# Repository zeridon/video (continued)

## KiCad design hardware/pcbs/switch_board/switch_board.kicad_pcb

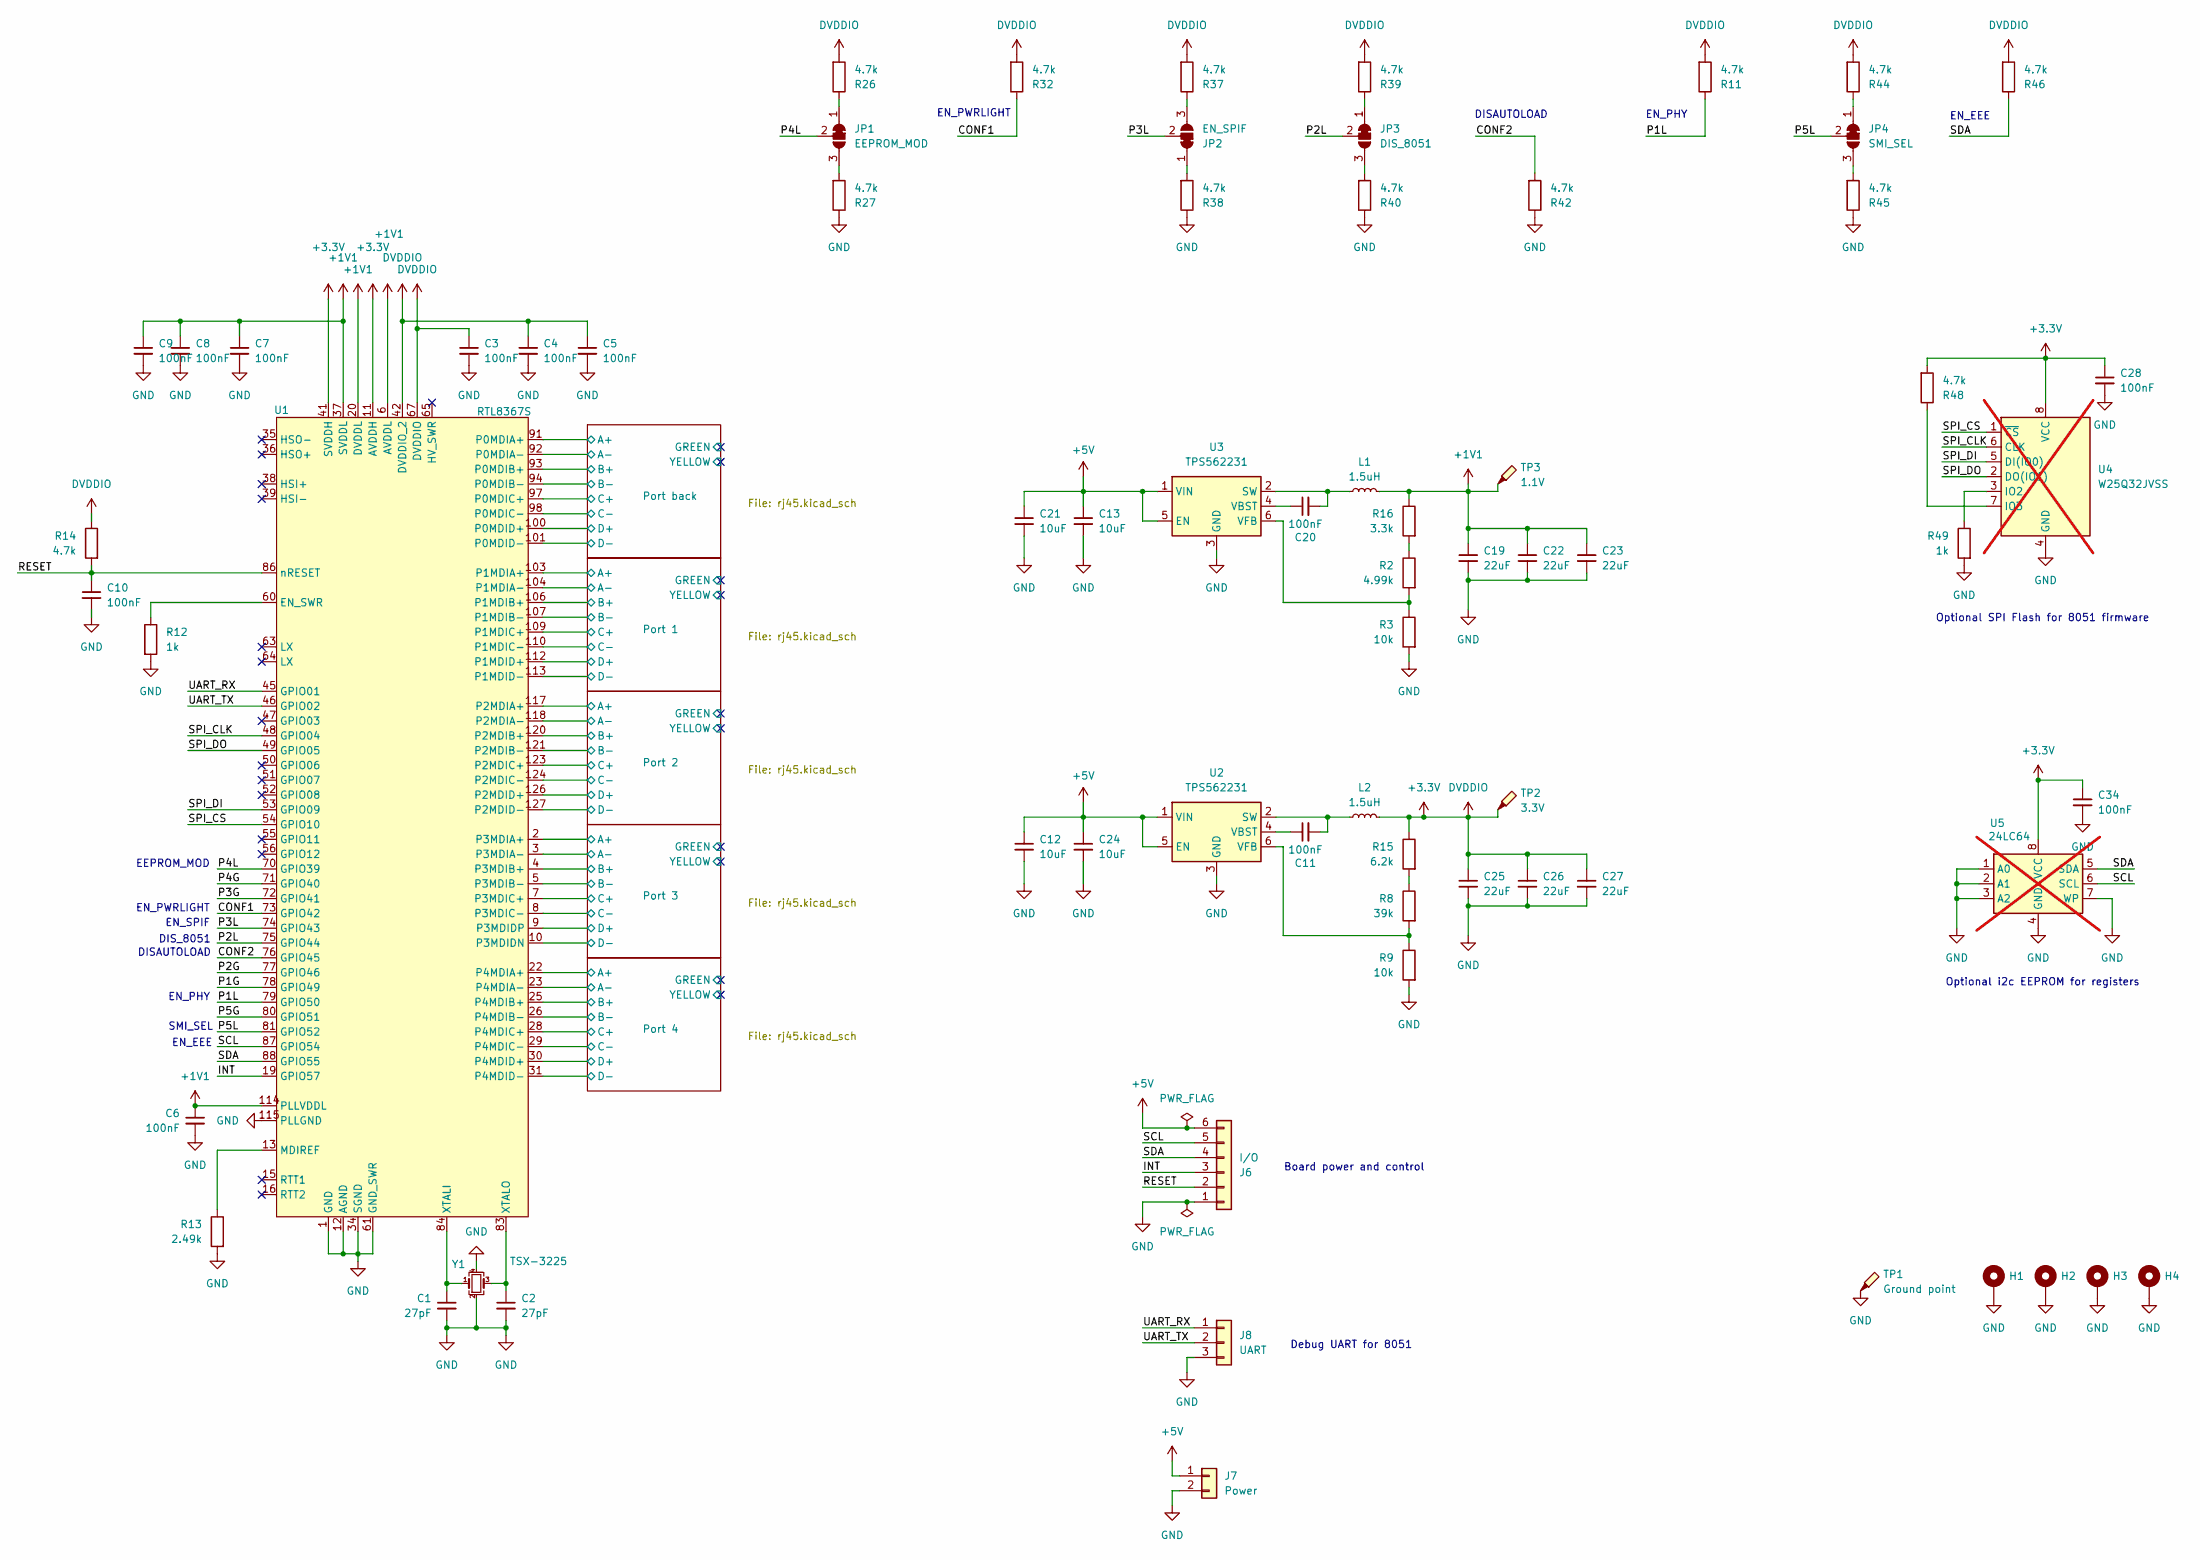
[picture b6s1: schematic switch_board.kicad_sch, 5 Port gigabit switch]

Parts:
C1, C2: 27pF; C_0603_1608Metric; Part C 27pF 16V 0603; LCSC C107045
C3, C4, C5, C6, C7, C8, C9, C10, C28, C34: 100nF; C_0603_1608Metric; Part C 100nF 16V 0603; LCSC C14663
C11, C20: 100nF; C_0603_1608Metric_Pad1.08x0.95mm_HandSolder; MPN 885012206126; LCSC C14663
C12, C13, C21, C24: 10uF; C_0603_1608Metric_Pad1.08x0.95mm_HandSolder; MPN 885012206126; LCSC C96446
C19, C22, C23, C25, C26, C27: 22uF; C_0603_1608Metric_Pad1.08x0.95mm_HandSolder; MPN 885012206126; LCSC C59461
H1, H2, H3, H4: MountingHole_Pad; MountingHole_3.2mm_M3_Pad_Via
J6: I/O; mta100_01x6_P2.54_647050-6; Part 640456-6; LCSC C86506
J7: Power; mta100_01x2_P2.54_647050-2; Part 640456-2; LCSC C86502
J8: UART; PinHeader_1x03_P1.00mm_Vertical
JP1: EEPROM_MOD; SolderJumper-3_P1.3mm_Bridged12_RoundedPad1.0x1.5mm
JP2: EN_SPIF; SolderJumper-3_P1.3mm_Bridged12_RoundedPad1.0x1.5mm
JP3: DIS_8051; SolderJumper-3_P1.3mm_Bridged12_RoundedPad1.0x1.5mm
JP4: SMI_SEL; SolderJumper-3_P1.3mm_Bridged12_RoundedPad1.0x1.5mm
L1, L2: 1.5uH; L_Taiyo-Yuden_MD-5050; Part BWVF005050201R5T00 or 74404054015; LCSC C702825
R2: 4.99k; R_0603_1608Metric; Part R 4.99kΩ 125mW 1% 0603; LCSC C23046
R3, R9: 10k; R_0603_1608Metric; Part R 10kΩ 125mW 1% 0603; LCSC C25804
R8: 39k; R_0603_1608Metric; Part R 39kΩ 125mW 1% 0603; LCSC C23153
R11, R14, R26, R27, R32, R37, R38, R39, R40, R42, R44, R45, R46, R48: 4.7k; R_0603_1608Metric; Part R 4.7kΩ 125mW 1% 0603; LCSC C23162
R12, R49: 1k; R_0603_1608Metric; Part R 1kΩ 125mW 1% 0603; LCSC C21190
R13: 2.49k; R_0402_1005Metric; Part R 2.49kΩ 125mW 1% 0402; LCSC C145071
R15: 6.2k; R_0603_1608Metric; Part R 6.2kΩ 125mW 1% 0603; LCSC C4160
R16: 3.3k; R_0603_1608Metric; Part R 3.3kΩ 125mW 1% 0603; LCSC C22978
TP1: Ground point; TestPoint_Bridge_Pitch2.54mm_Drill1.0mm
TP2: 3.3V; TestPoint_THTPad_2.0x2.0mm_Drill1.0mm
TP3: 1.1V; TestPoint_THTPad_2.0x2.0mm_Drill1.0mm
U1: RTL8367S; LQFP-128_14x14mm_P0.4mm; Part RTL8367S; LCSC C2760849
U2, U3: TPS562231; SOT-563; Part TPS562231DRLR; LCSC C2070899
U4: W25Q32JVSS; SOIC-8_5.23x5.23mm_P1.27mm; not fitted
U5: 24LC64; SOIC-8_3.9x4.9mm_P1.27mm; not fitted
Y1: TSX-3225; Crystal_SMD_SeikoEpson_TSX3225-4Pin_3.2x2.5mm; Part X322525MOB4SI; LCSC C9006

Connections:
+1V1: C6.1, C7.1, C8.1, C9.1, C19.1, C22.1, C23.1, L1.2, R16.1, TP3.1, U1.6 (AVDDL), U1.14 (AVDDL), U1.20 (DVDDL), U1.27 (AVDDL), U1.37 (SVDDL), U1.58 (DVDDL), U1.69 (DVDDL), U1.95 (AVDDL), U1.108 (AVDDL), U1.114 (PLLVDDL), U1.122 (AVDDL)
+3.3V: C3.1, C4.1, C5.1, C25.1, C26.1, C27.1, C28.1, C34.1, L2.2, R11.2, R14.1, R15.1, R26.2, R32.2, R37.2, R39.2, R44.2, R46.2, R48.2, TP2.1, U1.11 (AVDDH), U1.17 (AVDDH), U1.21 (AVDDH), U1.33 (AVDDH), U1.41 (SVDDH), U1.42 (DVDDIO_2), U1.59 (DVDDIO_2), U1.67 (DVDDIO), U1.82 (AVDDH), U1.90 (AVDDH), U1.102 (AVDDH), U1.116 (AVDDH), U1.128 (AVDDH), U4.8 (VCC), U5.8 (VCC)
+5V: C12.1, C13.1, C21.1, C24.1, J6.6, J7.1, U2.1 (VIN), U2.5 (EN), U3.1 (VIN), U3.5 (EN)
/CONF1: R32.1, U1.73 (GPIO42)
/CONF2: R42.2, U1.76 (GPIO45)
/INT: J6.3, U1.19 (GPIO57)
/P1G: U1.78 (GPIO49)
/P1L: R11.1, U1.79 (GPIO50)
/P2G: U1.77 (GPIO46)
/P2L: JP3.2 (C), U1.75 (GPIO44)
/P3G: U1.72 (GPIO41)
/P3L: JP2.2 (C), U1.74 (GPIO43)
/P4G: U1.71 (GPIO40)
/P4L: JP1.2 (C), U1.70 (GPIO39)
/P5G: U1.80 (GPIO51)
/P5L: JP4.2 (C), U1.81 (GPIO52)
/Port 1/A+: U1.103 (P1MDIA+); also elsewhere on the board
/Port 1/A-: U1.104 (P1MDIA-); also elsewhere on the board
/Port 1/B+: U1.106 (P1MDIB+); also elsewhere on the board
/Port 1/B-: U1.107 (P1MDIB-); also elsewhere on the board
/Port 1/C+: U1.109 (P1MDIC+); also elsewhere on the board
/Port 1/C-: U1.110 (P1MDIC-); also elsewhere on the board
/Port 1/D+: U1.112 (P1MDID+); also elsewhere on the board
/Port 1/D-: U1.113 (P1MDID-); also elsewhere on the board
/Port 2/A+: U1.117 (P2MDIA+); also elsewhere on the board
/Port 2/A-: U1.118 (P2MDIA-); also elsewhere on the board
/Port 2/B+: U1.120 (P2MDIB+); also elsewhere on the board
/Port 2/B-: U1.121 (P2MDIB-); also elsewhere on the board
/Port 2/C+: U1.123 (P2MDIC+); also elsewhere on the board
/Port 2/C-: U1.124 (P2MDIC-); also elsewhere on the board
/Port 2/D+: U1.126 (P2MDID+); also elsewhere on the board
/Port 2/D-: U1.127 (P2MDID-); also elsewhere on the board
/Port 3/A+: U1.2 (P3MDIA+); also elsewhere on the board
/Port 3/A-: U1.3 (P3MDIA-); also elsewhere on the board
/Port 3/B+: U1.4 (P3MDIB+); also elsewhere on the board
/Port 3/B-: U1.5 (P3MDIB-); also elsewhere on the board
/Port 3/C+: U1.7 (P3MDIC+); also elsewhere on the board
/Port 3/C-: U1.8 (P3MDIC-); also elsewhere on the board
/Port 3/D+: U1.9 (P3MDIDP); also elsewhere on the board
/Port 3/D-: U1.10 (P3MDIDN); also elsewhere on the board
/Port 4/A+: U1.22 (P4MDIA+); also elsewhere on the board
/Port 4/A-: U1.23 (P4MDIA-); also elsewhere on the board
/Port 4/B+: U1.25 (P4MDIB+); also elsewhere on the board
/Port 4/B-: U1.26 (P4MDIB-); also elsewhere on the board
/Port 4/C+: U1.28 (P4MDIC+); also elsewhere on the board
/Port 4/C-: U1.29 (P4MDIC-); also elsewhere on the board
/Port 4/D+: U1.30 (P4MDID+); also elsewhere on the board
/Port 4/D-: U1.31 (P4MDID-); also elsewhere on the board
/Port back/A+: U1.91 (P0MDIA+); also elsewhere on the board
/Port back/A-: U1.92 (P0MDIA-); also elsewhere on the board
/Port back/B+: U1.93 (P0MDIB+); also elsewhere on the board
/Port back/B-: U1.94 (P0MDIB-); also elsewhere on the board
/Port back/C+: U1.97 (P0MDIC+); also elsewhere on the board
/Port back/C-: U1.98 (P0MDIC-); also elsewhere on the board
/Port back/D+: U1.100 (P0MDID+); also elsewhere on the board
/Port back/D-: U1.101 (P0MDID-); also elsewhere on the board
/RESET: C10.1, J6.2, R14.2, U1.86 (nRESET)
/SCL: J6.5, U1.87 (GPIO54), U5.6 (SCL)
/SDA: J6.4, R46.1, U1.88 (GPIO55), U5.5 (SDA)
/SPI_CLK: U1.48 (GPIO04), U4.6 (CLK)
/SPI_CS: U1.54 (GPIO10), U4.1 (~CS)
/SPI_DI: U1.53 (GPIO09), U4.5 (DI(IO0))
/SPI_DO: U1.49 (GPIO05), U4.2 (DO(IO1))
/UART_RX: J8.1, U1.45 (GPIO01)
/UART_TX: J8.2, U1.46 (GPIO02)
GND: C1.2, C2.2, C3.2, C4.2, C5.2, C6.2, C7.2, C8.2, C9.2, C10.2, C12.2, C13.2, C19.2, C21.2, C22.2, C23.2, C24.2, C25.2, C26.2, C27.2, C28.2, C34.2, H1.1, H2.1, H3.1, H4.1, J6.1, J7.2, J8.3, R3.2, R9.2, R12.2, R13.2, R27.1, R38.1, R40.1, R42.1, R45.1, R49.2, TP1.1, U1.1 (GND), U1.12 (AGND), U1.18 (GND), U1.24 (GND), U1.32 (GND), U1.34 (SGND), U1.40 (SGND), U1.43 (GND), U1.44 (GND), U1.57 (GND), U1.61 (GND_SWR), U1.62 (GND_SWR), U1.68 (GND), U1.85 (GND), U1.89 (GND), U1.96 (GND), U1.99 (GND), U1.105 (GND), U1.111 (GND), U1.115 (PLLGND), U1.119 (GND), U1.125 (GND), U2.3 (GND), U3.3 (GND), U4.4 (GND), U5.1 (A0), U5.2 (A1), U5.3 (A2), U5.4 (GND), U5.7 (WP), Y1.2, Y1.4; also elsewhere on the board
unnamed: JP1.1 (A), R26.1
unnamed: JP1.3 (B), R27.2
unnamed: JP2.1 (A), R38.2
unnamed: JP2.3 (B), R37.1
unnamed: JP3.1 (A), R39.1
unnamed: JP3.3 (B), R40.2
unnamed: JP4.1 (A), R44.1
unnamed: JP4.3 (B), R45.2
unnamed: R8.1, R15.2
unnamed: R2.1, R16.2
unnamed: R12.1, U1.60 (EN_SWR)
unnamed: R13.1, U1.13 (MDIREF)
unnamed: C1.1, U1.84 (XTALI), Y1.1
unnamed: C2.1, U1.83 (XTALO), Y1.3
unnamed: C11.2, L2.1, U2.2 (SW)
unnamed: C11.1, U2.4 (VBST)
unnamed: R8.2, R9.1, U2.6 (VFB)
unnamed: C20.2, L1.1, U3.2 (SW)
unnamed: C20.1, U3.4 (VBST)
unnamed: R2.2, R3.1, U3.6 (VFB)
unnamed: R49.1, U4.3 (IO2)
unnamed: R48.1, U4.7 (IO3)

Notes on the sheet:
EN_EEE
Board power and control
EN_PWRLIGHT
Optional i2c EEPROM for registers
DISAUTOLOAD
SMI_SEL
EN_PHY
EN_SPIF
Debug UART for 8051
Optional SPI Flash for 8051 firmware
EEPROM_MOD
DIS_8051

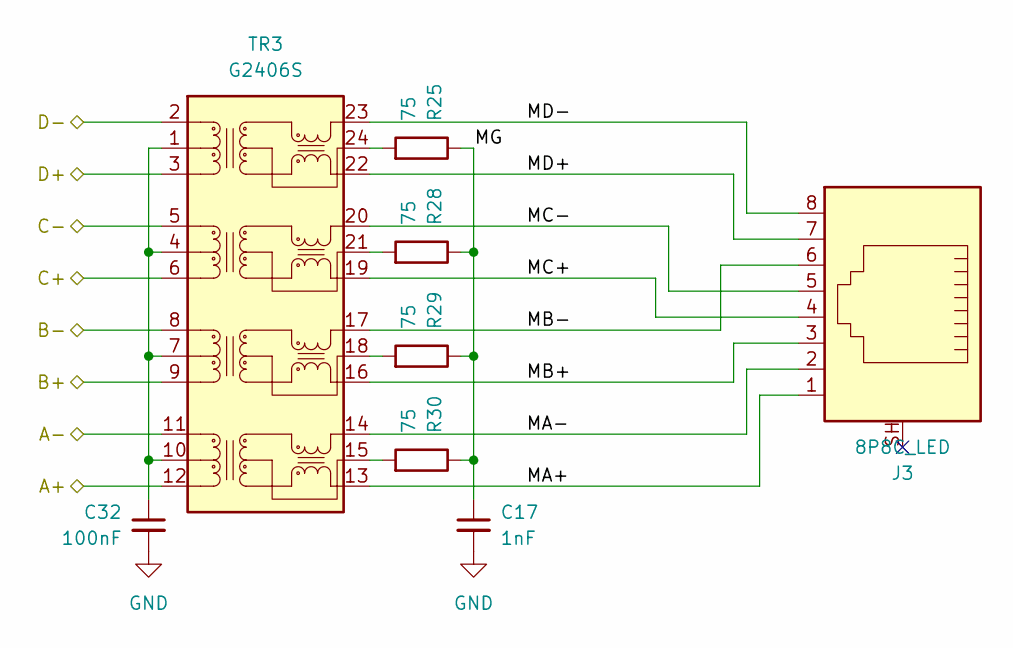
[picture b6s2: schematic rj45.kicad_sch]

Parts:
C17: 1nF; C_0603_1608Metric; Part C 1nF 16V 0603; LCSC C1588
C32: 100nF; C_0603_1608Metric; Part C 100nF 16V 0603; LCSC C14663
J3: 8P8C_LED; Heling MJ88-B211-JRS3; Part MJ88-B211-JRS3; LCSC C2895614
R25, R28, R29, R30: 75; R_0603_1608Metric; Part R 75Ω 125mW 1% 0603; LCSC C4275
TR3: G2406S; Part G2406S; LCSC C507595

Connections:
/Port 3/A+: TR3.12 (TD4-); also elsewhere on the board
/Port 3/A-: TR3.11 (TD4+); also elsewhere on the board
/Port 3/B+: TR3.9 (TD3-); also elsewhere on the board
/Port 3/B-: TR3.8 (TD3+); also elsewhere on the board
/Port 3/C+: TR3.6 (TD2-); also elsewhere on the board
/Port 3/C-: TR3.5 (TD2+); also elsewhere on the board
/Port 3/D+: TR3.3 (TD1-); also elsewhere on the board
/Port 3/D-: TR3.2 (TD1+); also elsewhere on the board
/Port 3/MA+: J3.1, TR3.13 (MX4-)
/Port 3/MA-: J3.2, TR3.14 (MX4+)
/Port 3/MB+: J3.3, TR3.16 (MX3-)
/Port 3/MB-: J3.6, TR3.17 (MX3+)
/Port 3/MC+: J3.4, TR3.19 (MX2-)
/Port 3/MC-: J3.5, TR3.20 (MX2+)
/Port 3/MD+: J3.7, TR3.22 (MX1-)
/Port 3/MD-: J3.8, TR3.23 (MX1+)
/Port 3/MG: C17.1, R25.1, R28.1, R29.1, R30.1
GND: C17.2, C32.2; also elsewhere on the board
unnamed: C32.1, TR3.1 (CT), TR3.4 (CT), TR3.7 (CT), TR3.10 (CT)
unnamed: R25.2, TR3.24 (CT)
unnamed: R28.2, TR3.21 (CT)
unnamed: R29.2, TR3.18 (CT)
unnamed: R30.2, TR3.15 (CT)

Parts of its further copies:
C14, C15, C16, C18: 1nF; C_0603_1608Metric; Part C 1nF 16V 0603; LCSC C1588
C29, C30, C31, C33: 100nF; C_0603_1608Metric; Part C 100nF 16V 0603; LCSC C14663
J1, J2, J4, J5: 8P8C_LED; Heling MJ88-B211-JRS3; Part MJ88-B211-JRS3; LCSC C2895614
R1, R4, R5, R6, R7, R10, R17, R20, R21, R22, R23, R24, R31, R34, R35, R36: 75; R_0603_1608Metric; Part R 75Ω 125mW 1% 0603; LCSC C4275
TR1, TR2, TR4, TR5: G2406S; Part G2406S; LCSC C507595

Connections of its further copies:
/Port 1/A+: TR1.12 (TD4-); also elsewhere on the board
/Port 1/A-: TR1.11 (TD4+); also elsewhere on the board
/Port 1/B+: TR1.9 (TD3-); also elsewhere on the board
/Port 1/B-: TR1.8 (TD3+); also elsewhere on the board
/Port 1/C+: TR1.6 (TD2-); also elsewhere on the board
/Port 1/C-: TR1.5 (TD2+); also elsewhere on the board
/Port 1/D+: TR1.3 (TD1-); also elsewhere on the board
/Port 1/D-: TR1.2 (TD1+); also elsewhere on the board
/Port 1/MA+: J1.1, TR1.13 (MX4-)
/Port 1/MA-: J1.2, TR1.14 (MX4+)
/Port 1/MB+: J1.3, TR1.16 (MX3-)
/Port 1/MB-: J1.6, TR1.17 (MX3+)
/Port 1/MC+: J1.4, TR1.19 (MX2-)
/Port 1/MC-: J1.5, TR1.20 (MX2+)
/Port 1/MD+: J1.7, TR1.22 (MX1-)
/Port 1/MD-: J1.8, TR1.23 (MX1+)
/Port 1/MG: C15.1, R1.1, R4.1, R5.1, R6.1
/Port 2/A+: TR2.12 (TD4-); also elsewhere on the board
/Port 2/A-: TR2.11 (TD4+); also elsewhere on the board
/Port 2/B+: TR2.9 (TD3-); also elsewhere on the board
/Port 2/B-: TR2.8 (TD3+); also elsewhere on the board
/Port 2/C+: TR2.6 (TD2-); also elsewhere on the board
/Port 2/C-: TR2.5 (TD2+); also elsewhere on the board
/Port 2/D+: TR2.3 (TD1-); also elsewhere on the board
/Port 2/D-: TR2.2 (TD1+); also elsewhere on the board
/Port 2/MA+: J2.1, TR2.13 (MX4-)
/Port 2/MA-: J2.2, TR2.14 (MX4+)
/Port 2/MB+: J2.3, TR2.16 (MX3-)
/Port 2/MB-: J2.6, TR2.17 (MX3+)
/Port 2/MC+: J2.4, TR2.19 (MX2-)
/Port 2/MC-: J2.5, TR2.20 (MX2+)
/Port 2/MD+: J2.7, TR2.22 (MX1-)
/Port 2/MD-: J2.8, TR2.23 (MX1+)
/Port 2/MG: C16.1, R7.1, R10.1, R23.1, R24.1
/Port 4/A+: TR4.12 (TD4-); also elsewhere on the board
/Port 4/A-: TR4.11 (TD4+); also elsewhere on the board
/Port 4/B+: TR4.9 (TD3-); also elsewhere on the board
/Port 4/B-: TR4.8 (TD3+); also elsewhere on the board
/Port 4/C+: TR4.6 (TD2-); also elsewhere on the board
/Port 4/C-: TR4.5 (TD2+); also elsewhere on the board
/Port 4/D+: TR4.3 (TD1-); also elsewhere on the board
/Port 4/D-: TR4.2 (TD1+); also elsewhere on the board
/Port 4/MA+: J4.1, TR4.13 (MX4-)
/Port 4/MA-: J4.2, TR4.14 (MX4+)
/Port 4/MB+: J4.3, TR4.16 (MX3-)
/Port 4/MB-: J4.6, TR4.17 (MX3+)
/Port 4/MC+: J4.4, TR4.19 (MX2-)
/Port 4/MC-: J4.5, TR4.20 (MX2+)
/Port 4/MD+: J4.7, TR4.22 (MX1-)
/Port 4/MD-: J4.8, TR4.23 (MX1+)
/Port 4/MG: C18.1, R31.1, R34.1, R35.1, R36.1
/Port back/A+: TR5.12 (TD4-); also elsewhere on the board
/Port back/A-: TR5.11 (TD4+); also elsewhere on the board
/Port back/B+: TR5.9 (TD3-); also elsewhere on the board
/Port back/B-: TR5.8 (TD3+); also elsewhere on the board
/Port back/C+: TR5.6 (TD2-); also elsewhere on the board
/Port back/C-: TR5.5 (TD2+); also elsewhere on the board
/Port back/D+: TR5.3 (TD1-); also elsewhere on the board
/Port back/D-: TR5.2 (TD1+); also elsewhere on the board
/Port back/MA+: J5.1, TR5.13 (MX4-)
/Port back/MA-: J5.2, TR5.14 (MX4+)
/Port back/MB+: J5.3, TR5.16 (MX3-)
/Port back/MB-: J5.6, TR5.17 (MX3+)
/Port back/MC+: J5.4, TR5.19 (MX2-)
/Port back/MC-: J5.5, TR5.20 (MX2+)
/Port back/MD+: J5.7, TR5.22 (MX1-)
/Port back/MD-: J5.8, TR5.23 (MX1+)
/Port back/MG: C14.1, R17.1, R20.1, R21.1, R22.1
GND: C14.2, C15.2, C16.2, C18.2, C29.2, C30.2, C31.2, C33.2; also elsewhere on the board
unnamed: C29.1, TR5.1 (CT), TR5.4 (CT), TR5.7 (CT), TR5.10 (CT)
unnamed: C30.1, TR1.1 (CT), TR1.4 (CT), TR1.7 (CT), TR1.10 (CT)
unnamed: C31.1, TR2.1 (CT), TR2.4 (CT), TR2.7 (CT), TR2.10 (CT)
unnamed: C33.1, TR4.1 (CT), TR4.4 (CT), TR4.7 (CT), TR4.10 (CT)
unnamed: R1.2, TR1.24 (CT)
unnamed: R4.2, TR1.21 (CT)
unnamed: R5.2, TR1.18 (CT)
unnamed: R6.2, TR1.15 (CT)
unnamed: R7.2, TR2.24 (CT)
unnamed: R10.2, TR2.21 (CT)
unnamed: R17.2, TR5.24 (CT)
unnamed: R20.2, TR5.21 (CT)
unnamed: R21.2, TR5.18 (CT)
unnamed: R22.2, TR5.15 (CT)
unnamed: R23.2, TR2.18 (CT)
unnamed: R24.2, TR2.15 (CT)
unnamed: R31.2, TR4.24 (CT)
unnamed: R34.2, TR4.21 (CT)
unnamed: R35.2, TR4.18 (CT)
unnamed: R36.2, TR4.15 (CT)

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
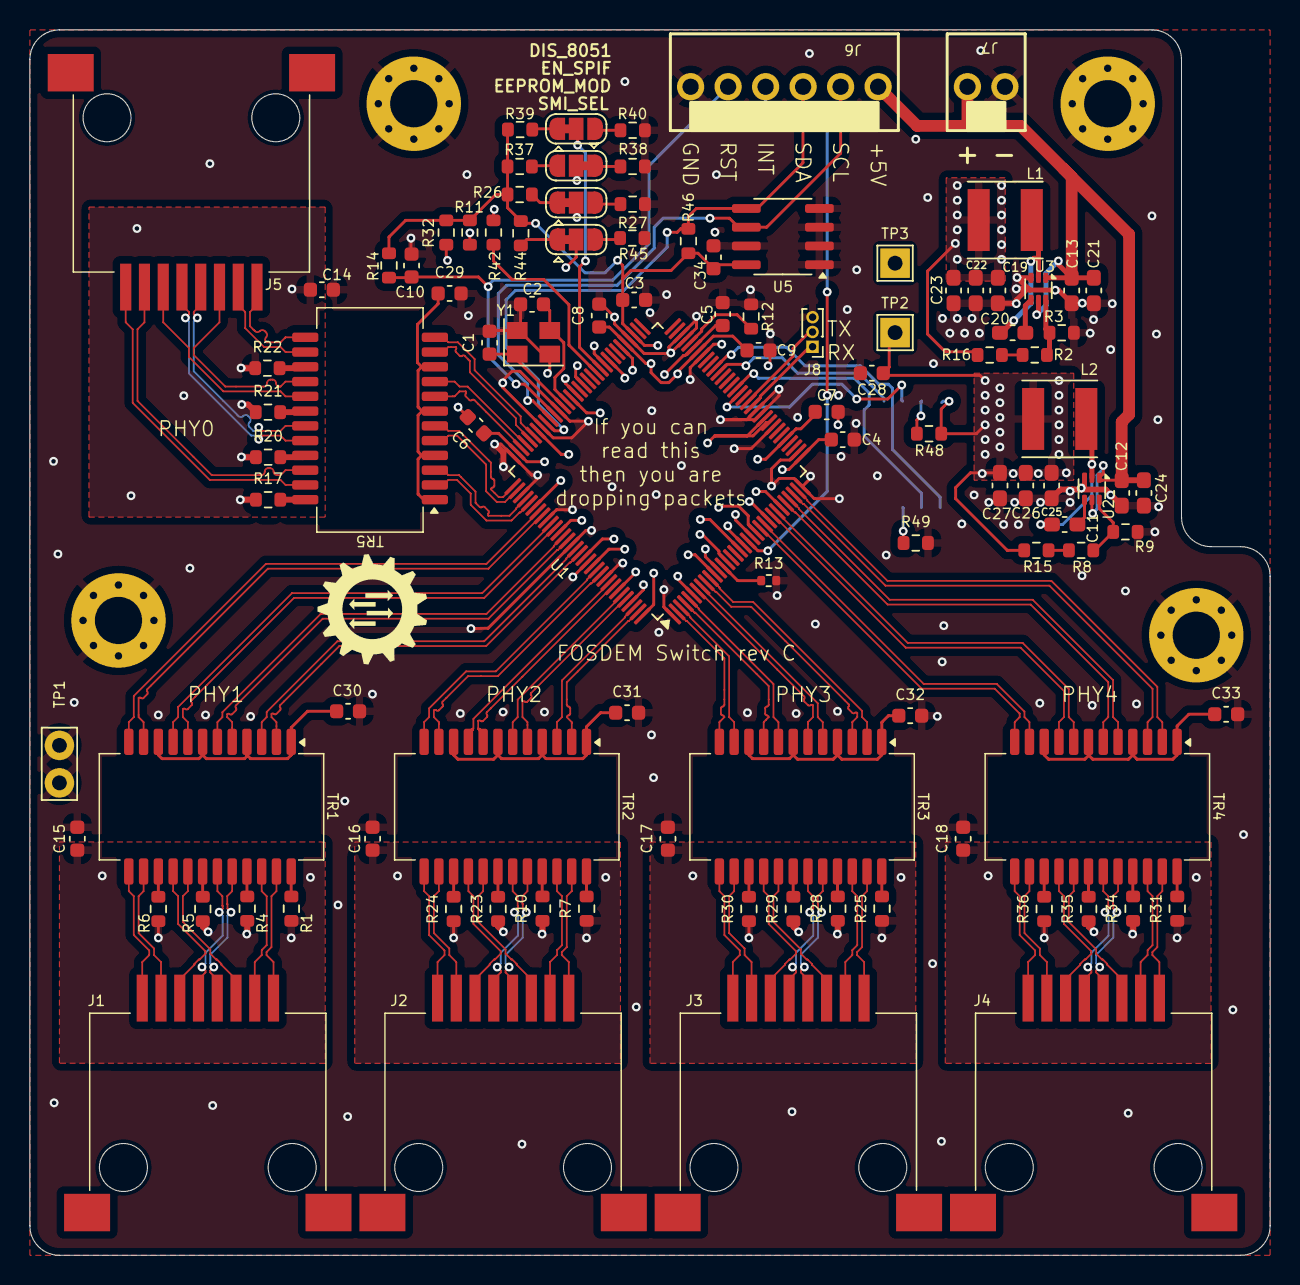
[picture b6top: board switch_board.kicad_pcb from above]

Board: 4 copper layers, 84.0 x 83.0 mm, 109 parts (1 on the bottom side), 153 nets.

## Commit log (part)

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2024-12-14 added screen bracket
2024-12-15 instructions: initial update for 2025
2024-12-16 added simplified screen bracket
2024-12-16 added stl files left and right
2024-12-16 corrected mirroring of mirror screen bracket for easier printinging
2024-12-16 added labels and extra hole to backpannel
2024-12-16 Amp to A
2024-12-16 moved screwholes in screenbracket 1mm mor appart
2024-12-20 layout cleanup: labels and logos
2024-12-20 fix colours for laser
2024-12-20 back plate: fix colour
2024-12-21 switch hdmi out label and connector
2024-12-21 back panel hdmi out connector slightly lower
2024-12-23 assembly: bootstrap assembly instructions
2024-12-23 assembly: jump-to-item experiment
2024-12-23 assembly: another experiment
2024-12-23 assembly: final experiment
2024-12-23 assembly: legend
2024-12-23 assembly: saner order
2024-12-23 assembly: bits of sweatshop organization
2024-12-24 assembly: update old box disassembly instructions
2024-12-24 assembly: fix typo
2024-12-24 assembly: add the mta100 marking steps in the sweatshop
2024-12-26 sweatshop: proper formatting
2024-12-27 finalise instructions
2024-12-27 assembly: some minor modifications
2024-12-27 assembly: clarify
2024-12-28 assembly: fix pic sizes
2024-12-29 assembly: fix display screw size
2024-12-29 Bring back the original fan_set_speed function for reference, while still being unused
2024-12-29 Change max fan RPM so that it's achievable
2024-12-29 Move pb.i2c.dump_all_regs from pwr_brd_ctl to commands
2024-12-29 Rework fan control algorithm
    - calculate next command time instead of saving the last one
    - cap the PWM output
    - add delay when spinning down the fans so that a correct RPM can be measured
    - update algorithm documentation
2024-12-29 Add edge case for zero fan RPM
2024-12-29 Move pb.i2c.scan from pwr_brd_ctl to commands
2024-12-30 Fix slow PWM decrease on boot
2024-12-30 Split thresholds to lower and upper to prevent fan stalling
2024-12-30 audio_board: fix channel/bus name response addresses
2025-01-03 assembly: fix to match what was actually done
2025-01-03 assembly: add display
2025-01-03 hardware: sync the readme with 2025
2025-01-08 Add io_say_f for complex debug output
2025-01-13 box_firmware: rename fancontrol-related functions
2025-01-13 box_firmware: proper direction for charger pin
2025-01-13 box_firmware: implement status reading of gpio pins
2025-01-13 box_firmware: implement status command
2025-01-18 livestream: fix room list for 2025
2025-01-25 voctops: 2 extra for 2025
2025-01-25 hosts: add full hostname in A records
2025-01-26 add udev rules for debug port
2025-01-26 Revert "update room setup checklist template"
    This reverts commit 3ab67fe36c52e66a67f362c6df42b7c427913c89.
2025-01-27 instructions: room list for 2025
2025-01-27 instructions: update devroom manual for 2025
2025-01-27 Add section about how to package the per room boxes back up
2025-01-28 audio_board: fix blank display bug
2025-01-28 audio_board: extract teensy audio
    - move teensy audio to `teensyaudio.h`
    - allow bus and channel multipliers, appiled to the virtual mixer-matrix
2025-01-28 firmware: audio_board: enable SerialUSB1
    Teensy doesn't ship with a configuration with multiple serial ports and audio I/O so this adjusts the current one to have more serial ports
2025-01-28 audio_board: fix wrong type for display::draw_channel
2025-01-28 audio_board: expose mixer state to OSC
2025-01-28 audio_board: add /levels osc endpoint for all levels at once
2025-01-28 firmware: audio_board: Fix up USB interface/endpoint configuration
    The endpoint numbers are shared and shouldn't overlap
2025-01-28 audio_board: fix mute/unmute issue
2025-01-28 audio_board: dump crash report to debug uart on boot
2025-01-28 audio_board: add CrashReport decoding tool
2025-01-28 audio_board: add info endpoint
    - add `/info` endpoint that reports the mixer configuration
    - add `USE_` prefix to config macros, as DISPLAY is used by the teensy
    lib
2025-01-28 audio_board: update development flash.sh
2025-01-28 audio_board: move Audio System Design code to a seperate file
    This allows us to easily copy-paste it;
    Also, reformatting the file breaks the web UI, as coordinates are not being successfully read
2025-01-28 audio_board: replace pointers with references
2025-01-28 audio_board: separate audio from main
    Do not allow the code to blindly touch the real matrix, always go
    through the mute/multiplier calculations
2025-01-28 audio_board: extract display state
2025-01-28 audio_mixer: EEPROM support, channel muting and refactoring
    - allow saving the channel levels to EEPROM
    - allow muting and unmuting channels while keeping the original level
    intact
    - decouple the display logic
    - split the huge main.cpp file
2025-01-28 audio_board: Move source files to src/
2025-01-28 reformat with clang-format
2025-01-28 audio_board: fix forgotten ack
2025-01-29 circleci: add recipe for building firmware
2025-01-30 correctly list files in firmware dir
2025-01-30 box_firmware: update flash script to use gpio
2025-01-30 install find
2025-01-30 this is the proper package for find...
2025-01-31 audio_board: don't hang on crash
2025-01-31 livestream: fix year
2025-01-31 live.fosdem.org: 2024->2025
2025-01-31 Fix event date
2025-02-01 Create mpv_cycle
2025-02-02 Correct spelling mistakes
2025-02-02 Fix typos discovered by codespell
2025-02-02 livestream: rooms slugs are now just room names
2025-02-13 box_firmware: add flashing utility
2025-02-13 box_firmware: replace fan control algorithm again
2025-02-26 audio_board: switch vendor/cores to upstream
2025-02-26 audio_board: switch vendor/Audio to upstream
2025-02-27 audio_board: Add new submodules to firmware
2025-02-27 audio_board: patch in USB descriptor
2025-02-27 audio_board: Patch audio lib for multiple SGTL5000 chips
2025-02-27 audio_board: Add readout method on Mixer4
2025-03-08 Implement basic VLAN support for the FOSDEM switch
2025-03-09 build fixes: fix minor build bugs in fan_ctl
2025-03-09 try using an archlinux-based circleci image
2025-03-09 build_fixes: add openssh dependency
2025-03-27 mixercontrol was moved to another repo
2025-06-10 move xlr_tester to audio_experiments/
2025-06-10 add taa3040 experiment board
2025-06-10 replicate frontend layout
2025-06-10 test pcb almost done
2025-06-12 finalise board
2025-07-02 Add WIP dual capture device PCB
2025-08-08 update bom
2025-09-19 hardware: improved fan bracket
2025-10-26 schematic cosmetics
2025-10-26 fix libraries
2025-10-26 final touches to libraries
2025-10-26 some placement
2025-10-27 add vias and mask to ic packages and route dac
2025-10-27 route one input
2025-10-27 route all ADC inputs
2025-10-28 some more routing
2025-10-28 routing almost complete
2025-10-29 fix XLR courtyard
2025-10-29 connect some items
2025-10-29 finish routing
2025-10-29 more font fixes
2025-10-29 component values
2025-10-30 revise BOM
2025-10-30 some silkscreen
2025-10-30 fix all silkscreens
2025-10-30 finish silkscreens
2025-10-30 slew rate limiting resistors
2025-10-30 add XLR logo
2025-10-30 final touches before production
2025-11-15 bump revision
2025-11-15 fix mistakes in audioboard design
2025-11-15 audio_board: we're starting to use the PC input
2025-11-15 properly change revision
2025-11-15 final run
2025-11-15 I have no idea what this is
2025-11-16 circleci: use a specific archlinux version
2025-11-16 instructions: update on which audio output port is used in all rooms
2025-11-16 box_rp2040: try to force a build on very new archlinux
2025-11-17 final fixes on audio board
2025-11-18 fix audioboard phantom power and some labels
2025-12-06 instructions: build fix & rebuild
2025-12-27 instructions: roomlist
2025-12-27 instructions: the control password is moved to pretalx
2025-12-27 instructions: remove the build for per-devroom sheet
2025-12-27 instructions: pre-built devroom manual
2025-12-31 Update instructions Makefile
    mk4ht handles cross-references gracefully, but pdflatex doesn't.
    replacing raw pdflatex with latexmk rebuilds the manual until it's
    stable and all references are stable.
2026-01-02 instructions: commit a built pdf
2026-01-03 instructions: odd numbered boxes - cam, even - slides
2026-01-04 instructions: manual merge from av-checklist-2025-update
2026-01-04 instructions: we have loudspeakers
2026-01-04 instructions: note on the cable with internet connectivity
2026-01-11 graph: updated overall drawings
    Just page 1, pages 2 and 3 are wrong.
2026-01-11 instructions: correct out port
2026-01-24 added second page to room setup checklist and added feedback line
2026-01-30 Check result of slip.read()
2026-01-30 This changes nothing
2026-01-31 Include USBSerial1 in the yield call
2026-02-08 instruction: initial update of the manual
    It's very out of date, even for 2026. Some initial clean up.
2026-02-14 instructions: try to include the setup checklist
2026-02-14 instructions: update, part 2
    * add the room checklist
    * add showbuilding explanation
    * some more text fixes
    * nicer margins
2026-02-14 instructions: more updates
2026-02-14 instructions: new build of the manuals
2026-02-21 instructions: fix warning
2026-02-21 instructions: add control.video main page
2026-02-21 instructions: formatting
2026-02-21 instructions: rebiult files
2026-03-20 circleci: build trixie packages
2026-03-20 add initial version of cli
2026-03-20 update large rooms cabling diagram; not yet fazantix based
2026-03-20 return levels
2026-03-20 reflect reality for cabling for small rooms
2026-03-20 update xxl room cabling diagrams
2026-03-20 update svg cabling diagrams
2026-03-20 floats
2026-03-20 Revert "update xxl cabling diagram"
    This reverts commit b2c5c2d0efcf3a724228f29534b8cbe64e58d27e.
2026-03-20 properly apply gains when reading from eeprom
2026-03-20 rename some stuff and remove osc shit
2026-03-20 more renames, proper gains
2026-03-21 digitalWrite
2026-03-21 arduino is hell
2026-03-21 fix gpios
2026-03-21 add video checklist typ
2026-03-21 remove obsolete canon camera stuff
2026-03-21 remove obsolete stuff
2026-03-21 add FOSDEM AV manual typst build instructions
2026-03-21 instructions for generating html
2026-03-21 proper debug logging
2026-03-21 more cli improvements
2026-03-21 slugs!
2026-03-21 debug print infra
2026-03-21 nuke the OSC stuff
2026-03-21 format code
2026-03-21 line length optimisation
2026-03-21 disable second serial
2026-03-21 config file parsing
2026-03-21 fix deadlocks
2026-03-21 proper failure handling
2026-03-21 state polling
2026-03-21 poll state and levels
2026-03-21 setters for matrix
2026-03-21 moar setters
2026-03-22 factory reset
2026-03-22 websocket support
2026-03-22 add web ui
2026-03-22 fix bugs
2026-03-22 add experimental ActivityPub server script for PeerTube
2026-03-23 Add digital gain control for the TAA3040
2026-03-28 implement sending of full state
2026-03-28 convert everything to decibels
2026-03-28 rename all db-related functions and clear up dbu/dbv etc
2026-03-28 split off serial ctl in preparation of fake ctl
2026-03-30 fix segfault
2026-04-04 properly handle dbs in fakectl
2026-04-04 some comments
2026-04-13 successfully perform a request
2026-04-13 initial working version of mixer frontend/backend connection
2026-04-14 ui works!
2026-04-17 documented api calls
2026-04-17 standoffs for mounting two hagibis
2026-04-22 update go deps
2026-04-22 add some readmes and todos
2026-04-22 fix bug in fakectl
2026-04-26 update misirka to version that uses buses
2026-04-27 clever build script
2026-04-27 mixer state deduplication
2026-04-28 audio ui: phantoms and sends
2026-04-28 audio ui: hide sliders and phantoms
2026-04-28 fix state copying bug in fakectl
2026-05-01 documentation prettification
2026-05-01 draft some marcel todos
2026-05-03 remove (most of) LaTeX stuff in favour of typst
2026-05-03 audioctl: MQTT backend support and better logging
2026-05-08 run linter to enforce go 1.24
2026-05-08 force go 1.24 and run linters and formatters
2026-05-08 audioctl_ui: working phantom
2026-05-08 audioctl_ui: pin misirka
2026-05-09 audioctl: basic debian packaging
2026-05-09 audioctl_ui: css / makefile fixes
2026-05-09 implement digital gain
2026-05-09 remove out-of-date limits in commands.cpp
